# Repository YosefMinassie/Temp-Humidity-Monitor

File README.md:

# Temperature & Humidity Monitor PCB

A custom PCB designed in KiCad that displays temperature and humidity data from a DHT22 sensor on an OLED display. The project uses an Arduino Nano as the main controller and includes a 10-segment LED bar graph for visual indicators, based on the temperature and humidity.

## Project Images

### Schematic

### PCB Layout

### 3D View + Rendered

## Components

- Arduino Nano
- DHT22 Temperature/Humidity Sensor
- 0.96" 128x64 I2C OLED Display
- 10-Segment LED Bar Graph
- 10 x 220Ω Resistors
- Custom PCB

## Why I Built This

I wanted to learn the complete PCB design process, from creating a schematic to designing a PCB and viewing the final board in 3D. This project also helped me practice working with sensors, displays, and KiCad.The project also would have a real purpose in my life because it helps my to manage my skin, eye, and nose health.

## Software/Websites Used

- KiCad for PCB design
- Arduino IDE to turn Wokwi Code into a .ano file
- Wokwi: To simulate my project and just to let you know, YOU NEED TRY THISS!!! IT'S AMAZING AND GIVES YOU A GREAT LEARNING EXPERIENCE OF WIRING & CODING!!!!; https://wokwi.com

---

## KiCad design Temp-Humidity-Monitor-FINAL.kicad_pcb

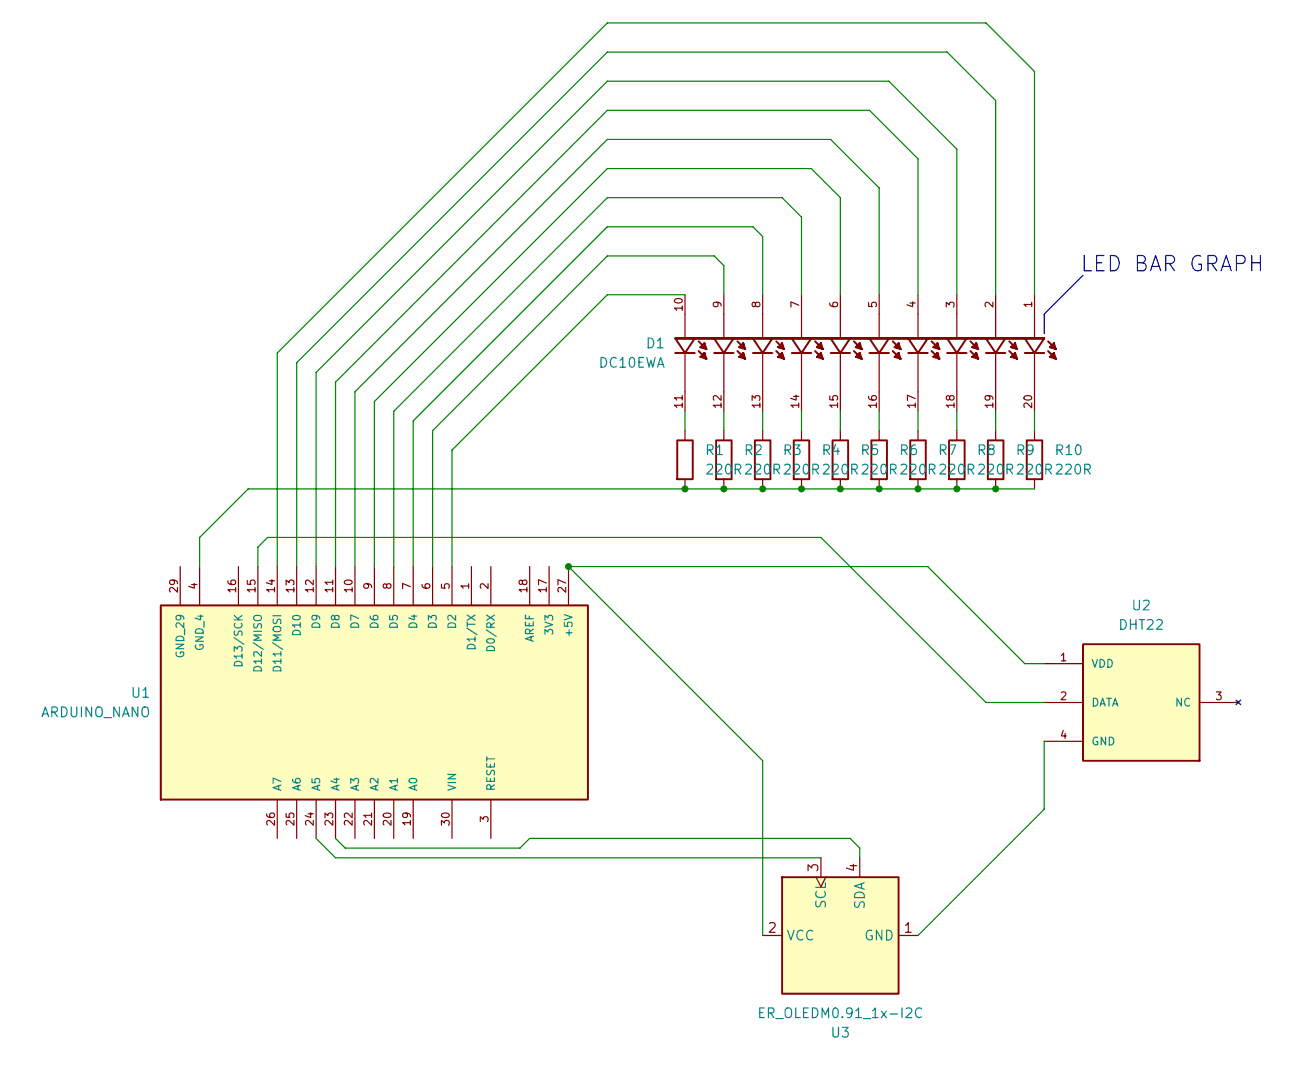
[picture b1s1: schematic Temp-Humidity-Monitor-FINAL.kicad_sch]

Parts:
D1: DC10EWA; DIP750W50P254L2540H825Q20; PARTREV V.10A
R1, R2, R3, R4, R5, R6, R7, R8, R9, R10: 220R; R_Axial_DIN0204_L3.6mm_D1.6mm_P5.08mm_Vertical
U1: ARDUINO_NANO; MODULE_ARDUINO_NANO; PARTREV 30/06/2021
U2: DHT22
U3: ER_OLEDM0.91_1x-I2C

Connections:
unnamed: D1.11, R1.1
unnamed: D1.12, R2.1
unnamed: D1.13, R3.1
unnamed: D1.14, R4.1
unnamed: D1.15, R5.1
unnamed: D1.16, R6.1
unnamed: D1.17, R7.1
unnamed: D1.18, R8.1
unnamed: D1.19, R9.1
unnamed: D1.20, R10.1
unnamed: U1.27 (+5V), U2.1 (VDD), U3.2 (VCC)
unnamed: U1.23 (A4), U3.4 (SDA)
unnamed: U1.24 (A5), U3.3 (SCL)
unnamed: D1.10, U1.5 (D2)
unnamed: D1.9, U1.6 (D3)
unnamed: D1.8, U1.7 (D4)
unnamed: D1.7, U1.8 (D5)
unnamed: D1.6, U1.9 (D6)
unnamed: D1.5, U1.10 (D7)
unnamed: D1.4, U1.11 (D8)
unnamed: D1.3, U1.12 (D9)
unnamed: D1.2, U1.13 (D10)
unnamed: D1.1, U1.14 (D11/MOSI)
unnamed: U1.15 (D12/MISO), U2.2 (DATA)
unnamed: R1.2, R2.2, R3.2, R4.2, R5.2, R6.2, R7.2, R8.2, R9.2, R10.2, U1.4 (GND_4)
unnamed: U1.3 (RESET), U1.28 (RESET)
unnamed: U2.4 (GND), U3.1 (GND)

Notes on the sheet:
LED BAR GRAPH

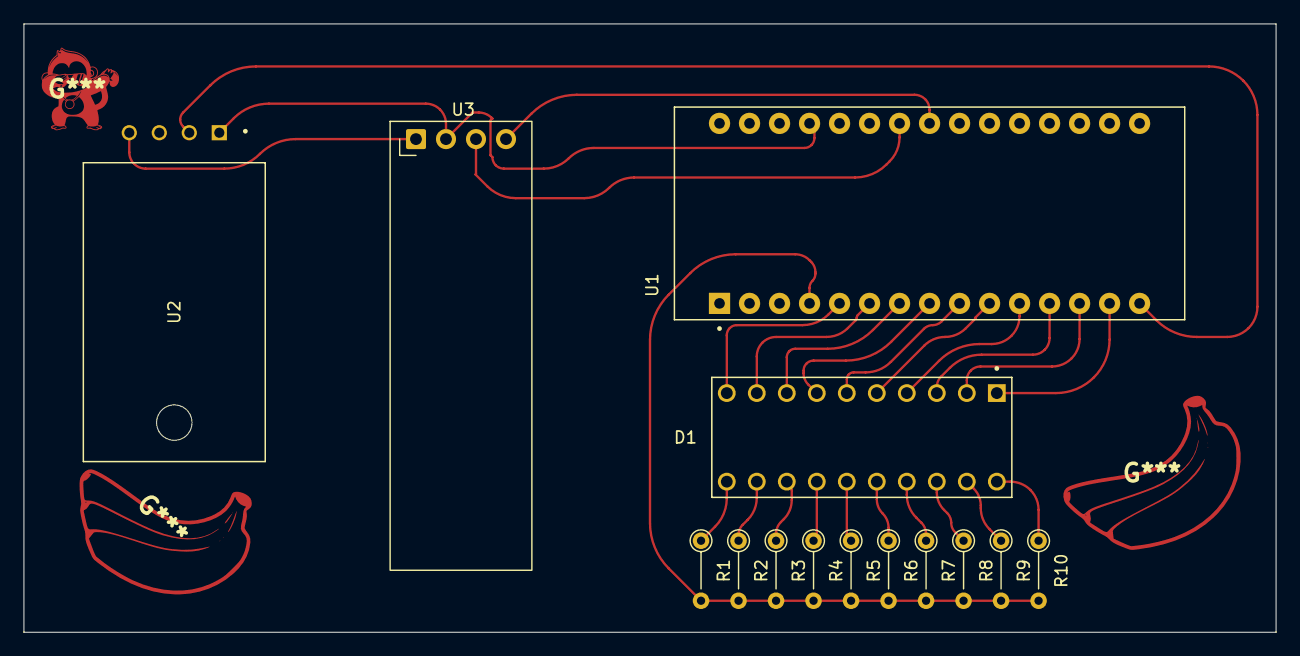
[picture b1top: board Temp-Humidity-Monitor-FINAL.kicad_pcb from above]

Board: 2 copper layers, 106.0 x 51.5 mm, 14 parts (0 on the bottom side), 27 nets.
